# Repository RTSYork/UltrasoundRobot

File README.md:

Ultrasonic Array for Maze Robot
----
Phil Greenland and Russell Joyce  
Department of Computer Science, University of York, UK

---

For more information, see http://rtslab.wikispaces.com/Ultrasonic+Array+for+Maze+Robot

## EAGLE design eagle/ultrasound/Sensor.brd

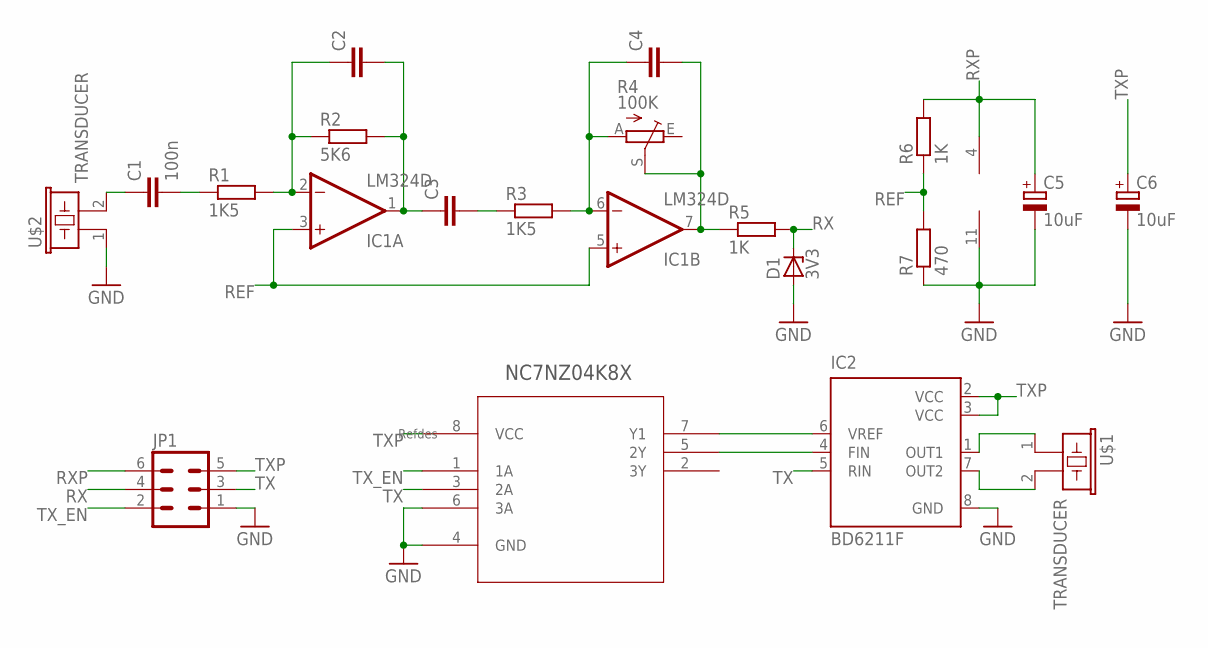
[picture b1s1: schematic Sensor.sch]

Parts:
C1: 100n; C0805
C2, C3, C4: C-EUC0805; C0805
C5, C6: 10uF; E2-5
D1: 3V3; ZDIO-2.5
IC1: LM324D; SO14
IC2: BD6211F; SOP8
JP1: MA03-2
R1, R3: 1K5; R0805
R2: 5K6; R0805
R4: 100K; S63P
R5, R6: 1K; R0805
R7: 470; R0805
U1: NC7NZ04K8X; SOP50P310X90-8N
U$1, U$2: TRANSDUCER

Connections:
GND: C5.-, C6.-, D1.A, IC1.11 (V-), IC2.8 (GND), JP1.1, R7.1, U1.4 (GND), U1.6 (3A), U$2.1
unnamed: C2.1, IC1.2 (-IN), R1.2, R2.1
unnamed: C1.2, R1.1
unnamed: C2.2, C3.1, IC1.1 (OUT), R2.2
unnamed: C3.2, R3.1
unnamed: C4.1, IC1.6 (-IN), R3.2, R4.A
unnamed: C4.2, IC1.7 (OUT), R4.S, R5.1
unnamed: C1.1, U$2.2
unnamed: IC2.1 (OUT1), U$1.1
unnamed: IC2.7 (OUT2), U$1.2
unnamed: IC2.6 (VREF), U1.7 (Y1)
unnamed: IC2.4 (FIN), U1.5 (2Y)
REF: IC1.3 (+IN), IC1.5 (+IN), R6.1, R7.2
RX: D1.C, JP1.4, R5.2
RXP: C5.+, IC1.4 (V+), JP1.6, R6.2
TX: IC2.5 (RIN), JP1.3, U1.3 (2A)
TXP: C6.+, IC2.2 (VCC), IC2.3 (VCC), JP1.5, U1.8 (VCC)
TX_EN: JP1.2, U1.1 (1A)

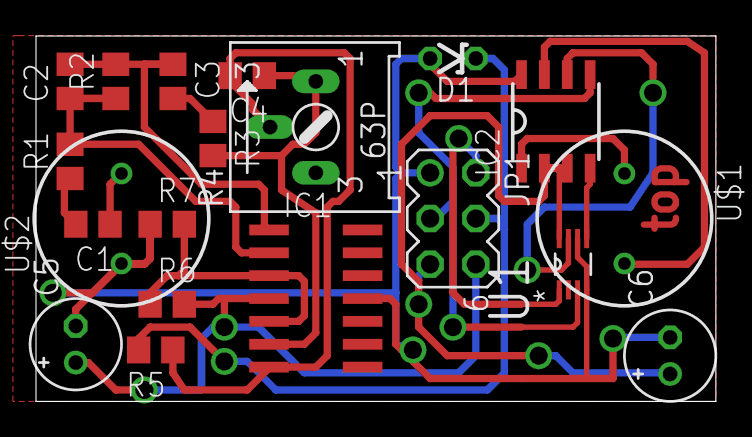
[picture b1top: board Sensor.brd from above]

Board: 2 copper layers, 37.8 x 20.3 mm, 20 parts (0 on the bottom side), 18 nets.

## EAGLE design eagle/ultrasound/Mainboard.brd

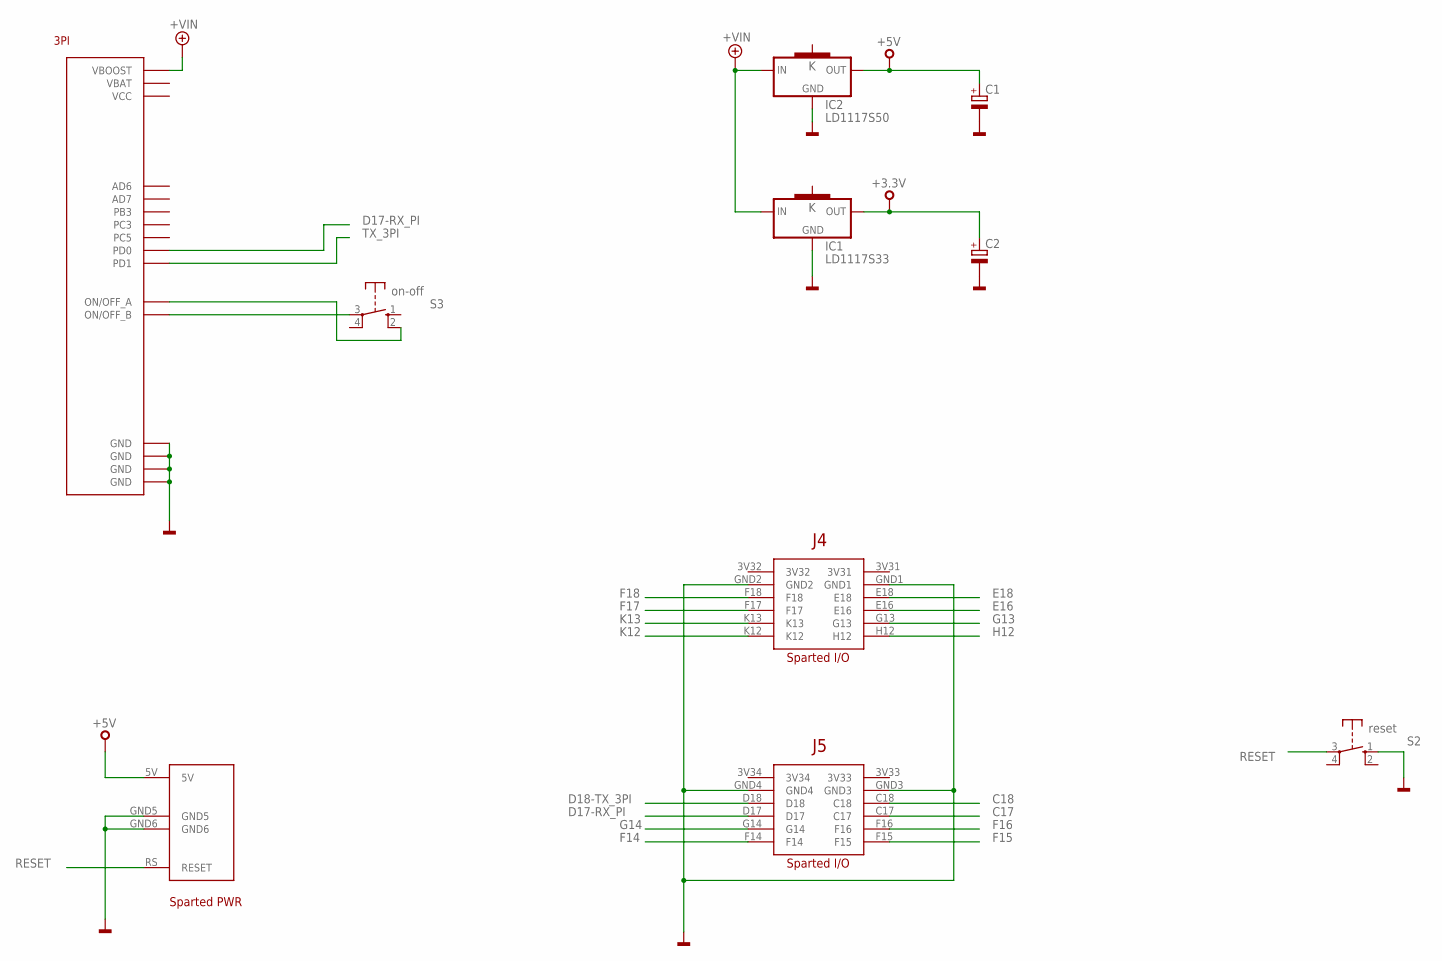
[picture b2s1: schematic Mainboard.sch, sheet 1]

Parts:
C1, C2: CPOL-EUE2.5-5; E2,5-5
IC1: LD1117S33; SOT223
IC2: LD1117S50; SOT223
S2: reset; DT6
S3: on-off; DT6
U$1: M3PI-NO-LCD
U$4: LX9

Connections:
+3,3V: C2.+, IC1.2 (OUT)
+5V: C1.+, IC2.2 (OUT), U$4.5V; also elsewhere on the board
+VIN: IC1.3 (IN), IC2.3 (IN), U$1.VBOOST
C17: U$4.C17; also elsewhere on the board
C18: U$4.C18; also elsewhere on the board
D17-RX_PI: U$1.PD0, U$4.D17
D18-TX_3PI: U$4.D18; also elsewhere on the board
E16: U$4.E16; also elsewhere on the board
E18: U$4.E18; also elsewhere on the board
F14: U$4.F14; also elsewhere on the board
F15: U$4.F15; also elsewhere on the board
F16: U$4.F16; also elsewhere on the board
F17: U$4.F17; also elsewhere on the board
F18: U$4.F18; also elsewhere on the board
G13: U$4.G13; also elsewhere on the board
G14: U$4.G14; also elsewhere on the board
GND: C1.-, C2.-, IC1.1 (GND), IC2.1 (GND), S2.1 (S), U$1.GND@1 (GND), U$1.GND@2 (GND), U$1.GND@3 (GND), U$1.GND@4 (GND), U$4.GND1, U$4.GND2, U$4.GND3, U$4.GND4, U$4.GND5, U$4.GND6; also elsewhere on the board
H12: U$4.H12; also elsewhere on the board
K12: U$4.K12; also elsewhere on the board
K13: U$4.K13; also elsewhere on the board
unnamed: S3.3, U$1.ON/OFF_B
unnamed: S3.2 (S), U$1.ON/OFF_A
RESET: S2.3, U$4.RS (RESET)
TX_3PI: U$1.PD1; also elsewhere on the board

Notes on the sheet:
Sparted I/O
Sparted PWR

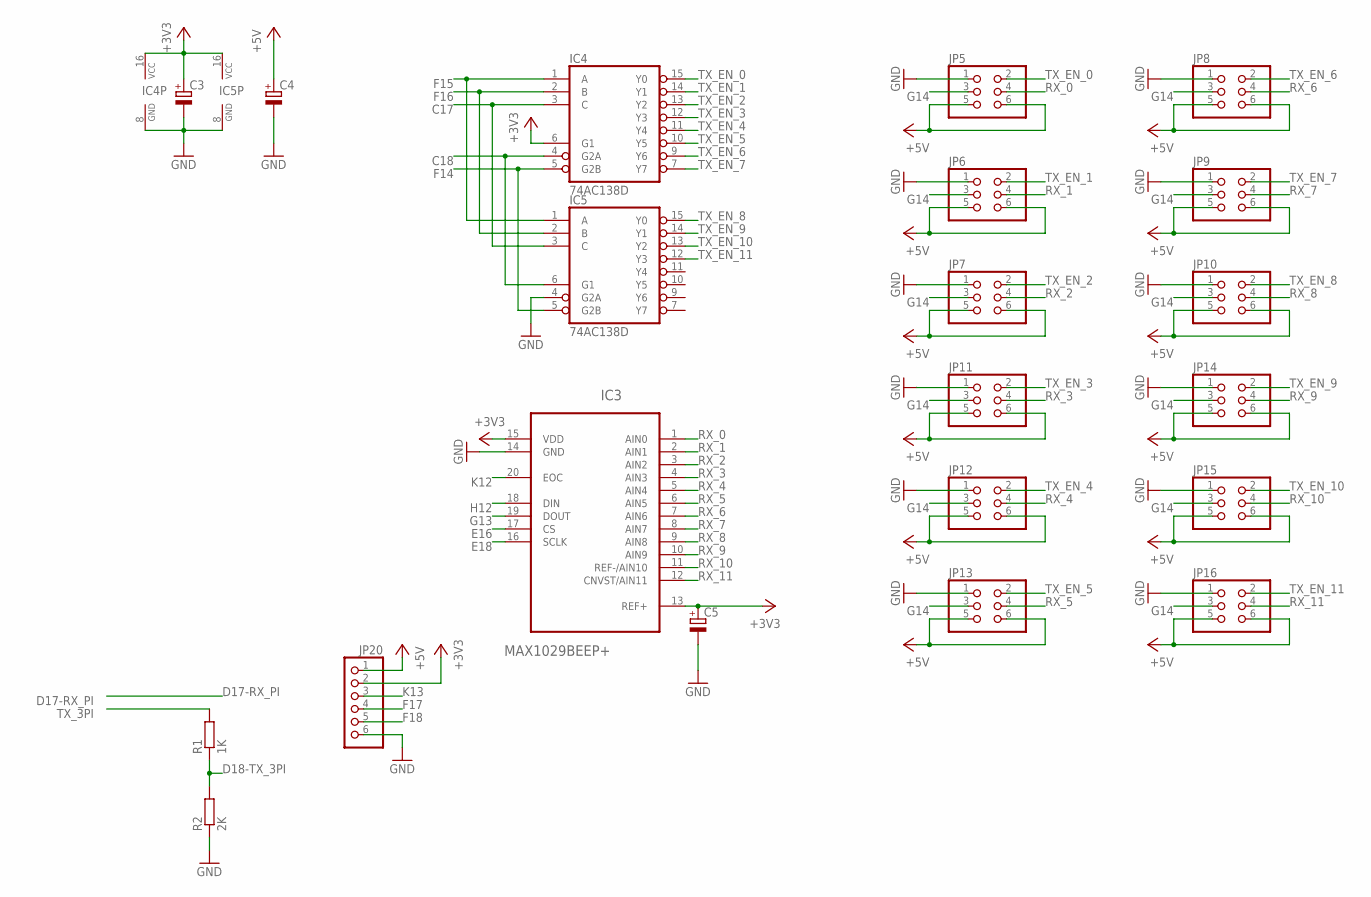
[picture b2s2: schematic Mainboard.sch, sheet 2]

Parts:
C3, C4, C5: CPOL-EUE2-5; E2-5
IC3: MAX1029BEEP+; SOP64P600X165-20N
IC4, IC5: 74AC138D; SO16
JP5, JP9: PINHD-2X3; 2X03
JP6, JP7, JP8, JP10, JP11, JP12, JP13, JP14, JP15, JP16: PINHD-2X3/90; 2X03/90
JP20: PINHD-1X6; 1X06
R1: 1K; R0805
R2: 2K; R0805

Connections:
+3V3: C3.+, C5.+, IC3.13 (REF+), IC3.15 (VDD), IC4.6 (G1), IC4.16 (VCC), IC5.16 (VCC), JP20.2
+5V: C4.+, JP5.5, JP5.6, JP6.5, JP6.6, JP7.5, JP7.6, JP8.5, JP8.6, JP9.5, JP9.6, JP10.5, JP10.6, JP11.5, JP11.6, JP12.5, JP12.6, JP13.5, JP13.6, JP14.5, JP14.6, JP15.5, JP15.6, JP16.5, JP16.6, JP20.1; also elsewhere on the board
C17: IC4.3 (C), IC5.3 (C); also elsewhere on the board
C18: IC4.4 (G2A), IC5.6 (G1); also elsewhere on the board
D18-TX_3PI: R1.1, R2.2; also elsewhere on the board
E16: IC3.17 (CS); also elsewhere on the board
E18: IC3.16 (SCLK); also elsewhere on the board
F14: IC4.5 (G2B), IC5.5 (G2B); also elsewhere on the board
F15: IC4.1 (A), IC5.1 (A); also elsewhere on the board
F16: IC4.2 (B), IC5.2 (B); also elsewhere on the board
F17: JP20.4; also elsewhere on the board
F18: JP20.5; also elsewhere on the board
G13: IC3.19 (DOUT); also elsewhere on the board
G14: JP5.3, JP6.3, JP7.3, JP8.3, JP9.3, JP10.3, JP11.3, JP12.3, JP13.3, JP14.3, JP15.3, JP16.3; also elsewhere on the board
GND: C3.-, C4.-, C5.-, IC3.14 (GND), IC4.8 (GND), IC5.4 (G2A), IC5.8 (GND), JP5.1, JP6.1, JP7.1, JP8.1, JP9.1, JP10.1, JP11.1, JP12.1, JP13.1, JP14.1, JP15.1, JP16.1, JP20.6, R2.1; also elsewhere on the board
H12: IC3.18 (DIN); also elsewhere on the board
K12: IC3.20 (EOC); also elsewhere on the board
K13: JP20.3; also elsewhere on the board
RX_0: IC3.1 (AIN0), JP5.4
RX_1: IC3.2 (AIN1), JP6.4
RX_2: IC3.3 (AIN2), JP7.4
RX_3: IC3.4 (AIN3), JP11.4
RX_4: IC3.5 (AIN4), JP12.4
RX_5: IC3.6 (AIN5), JP13.4
RX_6: IC3.7 (AIN6), JP8.4
RX_7: IC3.8 (AIN7), JP9.4
RX_8: IC3.9 (AIN8), JP10.4
RX_9: IC3.10 (AIN9), JP14.4
RX_10: IC3.11 (REF-/AIN10), JP15.4
RX_11: IC3.12 (CNVST/AIN11), JP16.4
TX_3PI: R1.2; also elsewhere on the board
TX_EN_0: IC4.15 (Y0), JP5.2
TX_EN_1: IC4.14 (Y1), JP6.2
TX_EN_2: IC4.13 (Y2), JP7.2
TX_EN_3: IC4.12 (Y3), JP11.2
TX_EN_4: IC4.11 (Y4), JP12.2
TX_EN_5: IC4.10 (Y5), JP13.2
TX_EN_6: IC4.9 (Y6), JP8.2
TX_EN_7: IC4.7 (Y7), JP9.2
TX_EN_8: IC5.15 (Y0), JP10.2
TX_EN_9: IC5.14 (Y1), JP14.2
TX_EN_10: IC5.13 (Y2), JP15.2
TX_EN_11: IC5.12 (Y3), JP16.2

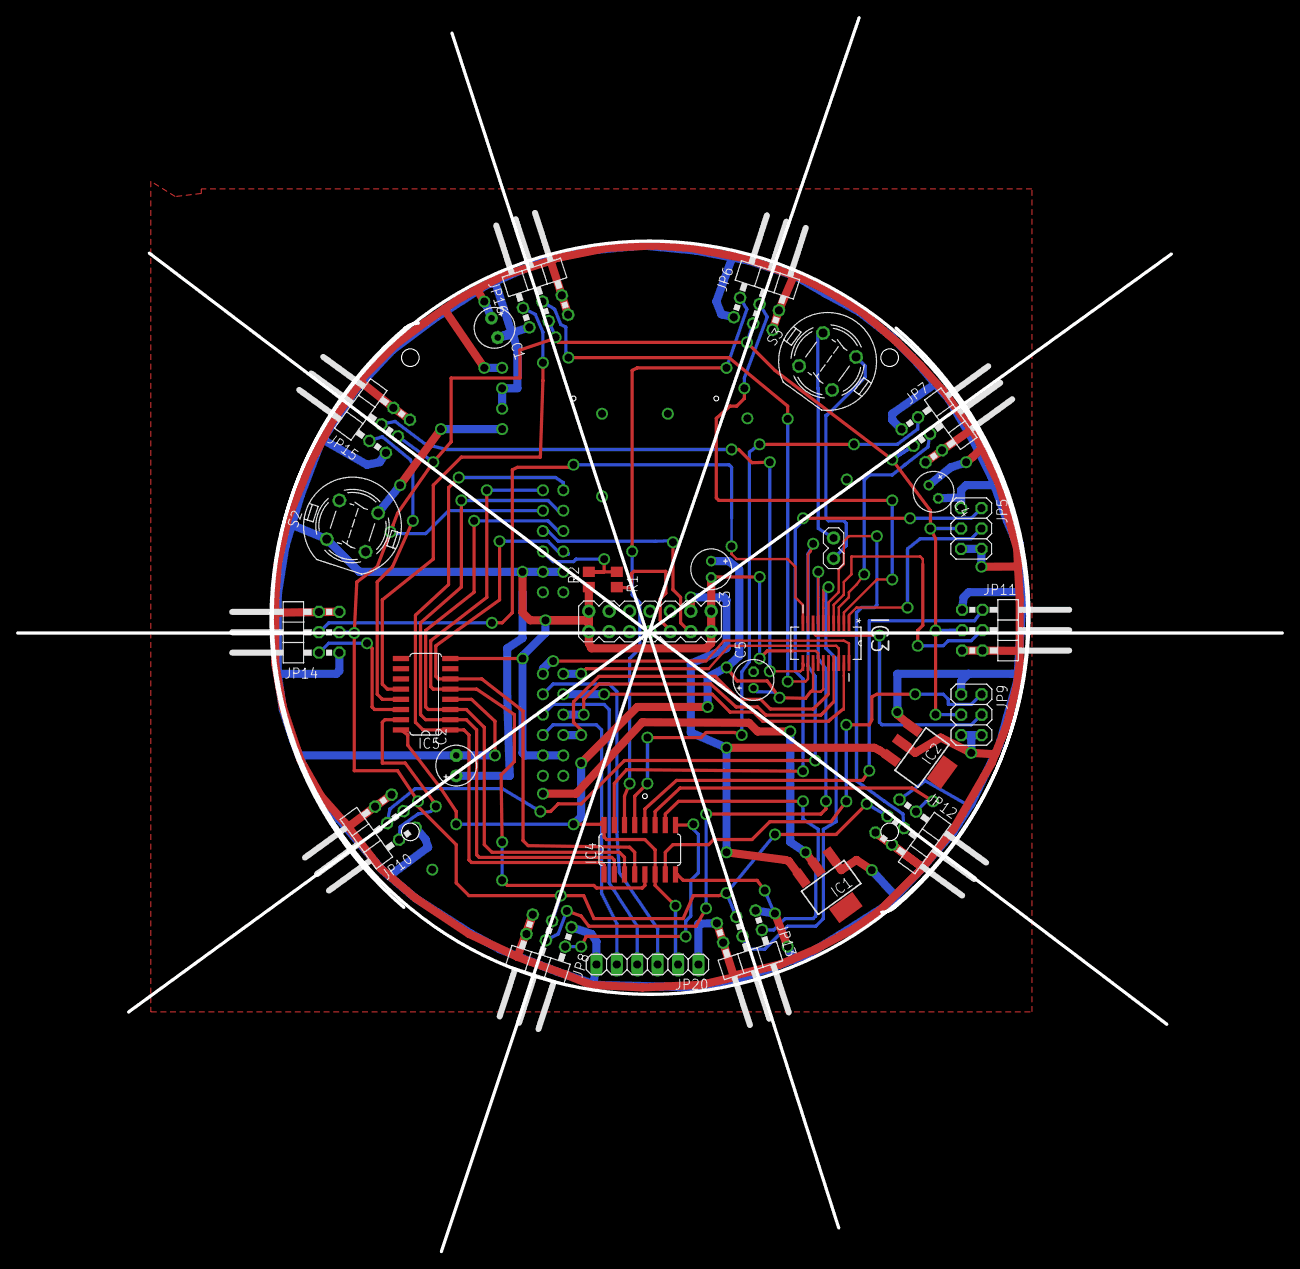
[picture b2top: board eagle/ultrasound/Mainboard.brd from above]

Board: 2 copper layers, 157.5 x 153.7 mm, 29 parts (1 on the bottom side), 49 nets.

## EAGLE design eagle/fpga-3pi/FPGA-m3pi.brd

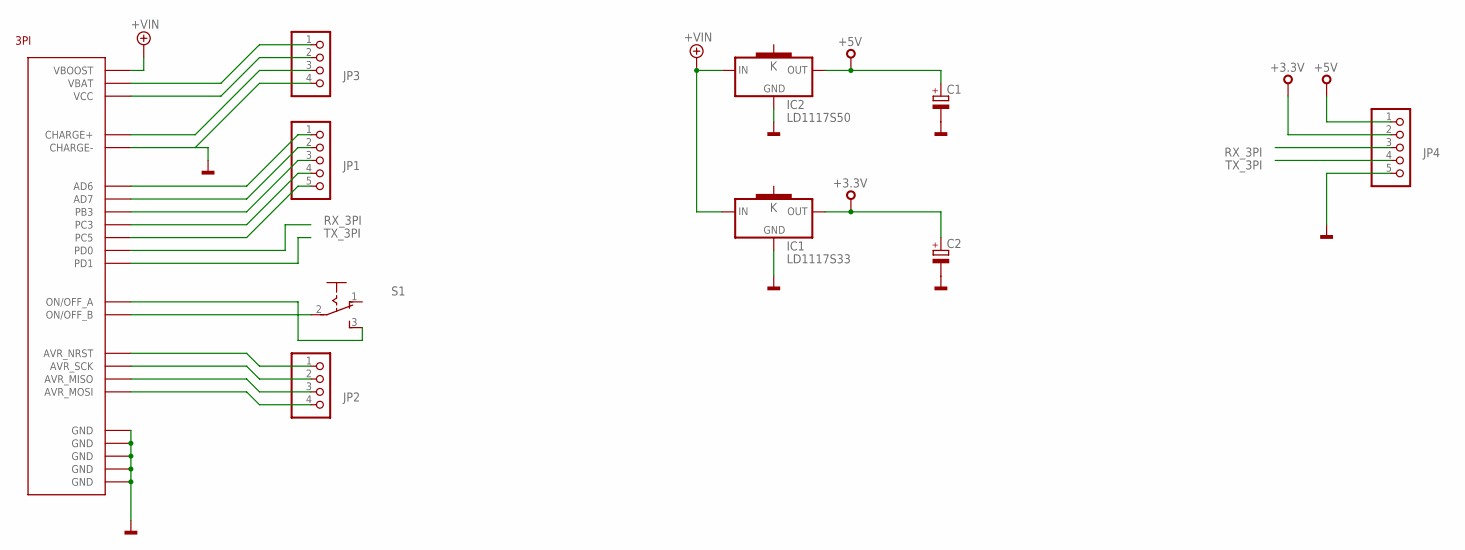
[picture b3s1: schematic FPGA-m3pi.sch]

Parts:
C1, C2: CPOL-EUE2.5-5; E2,5-5
IC1: LD1117S33; SOT223
IC2: LD1117S50; SOT223
JP1, JP4: PINHD-1X5; 1X05
JP2, JP3: PINHD-1X4; 1X04
S1: M251
U$1: MBED-M3PI_3PI

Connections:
+3,3V: C2.+, IC1.2 (OUT), JP4.2
+5V: C1.+, IC2.2 (OUT), JP4.1
+VIN: IC1.3 (IN), IC2.3 (IN), U$1.VBOOST
GND: C1.-, C2.-, IC1.1 (GND), IC2.1 (GND), JP3.4, JP4.5, U$1.CHARGE-, U$1.GND@1 (GND), U$1.GND@2 (GND), U$1.GND@3 (GND), U$1.GND@4 (GND), U$1.GND@5 (GND)
unnamed: JP1.1, U$1.AD6
unnamed: JP1.2, U$1.AD7
unnamed: S1.2, U$1.ON/OFF_B
unnamed: S1.3 (S), U$1.ON/OFF_A
unnamed: JP1.3, U$1.PB3
unnamed: JP1.4, U$1.PC3
unnamed: JP1.5, U$1.PC5
unnamed: JP2.1, U$1.AVR_NRST
unnamed: JP2.2, U$1.AVR_SCK
unnamed: JP2.3, U$1.AVR_MISO
unnamed: JP2.4, U$1.AVR_MOSI
unnamed: JP3.3, U$1.CHARGE+
unnamed: JP3.2, U$1.VCC
unnamed: JP3.1, U$1.VBAT
RX_3PI: JP4.3, U$1.PD0
TX_3PI: JP4.4, U$1.PD1

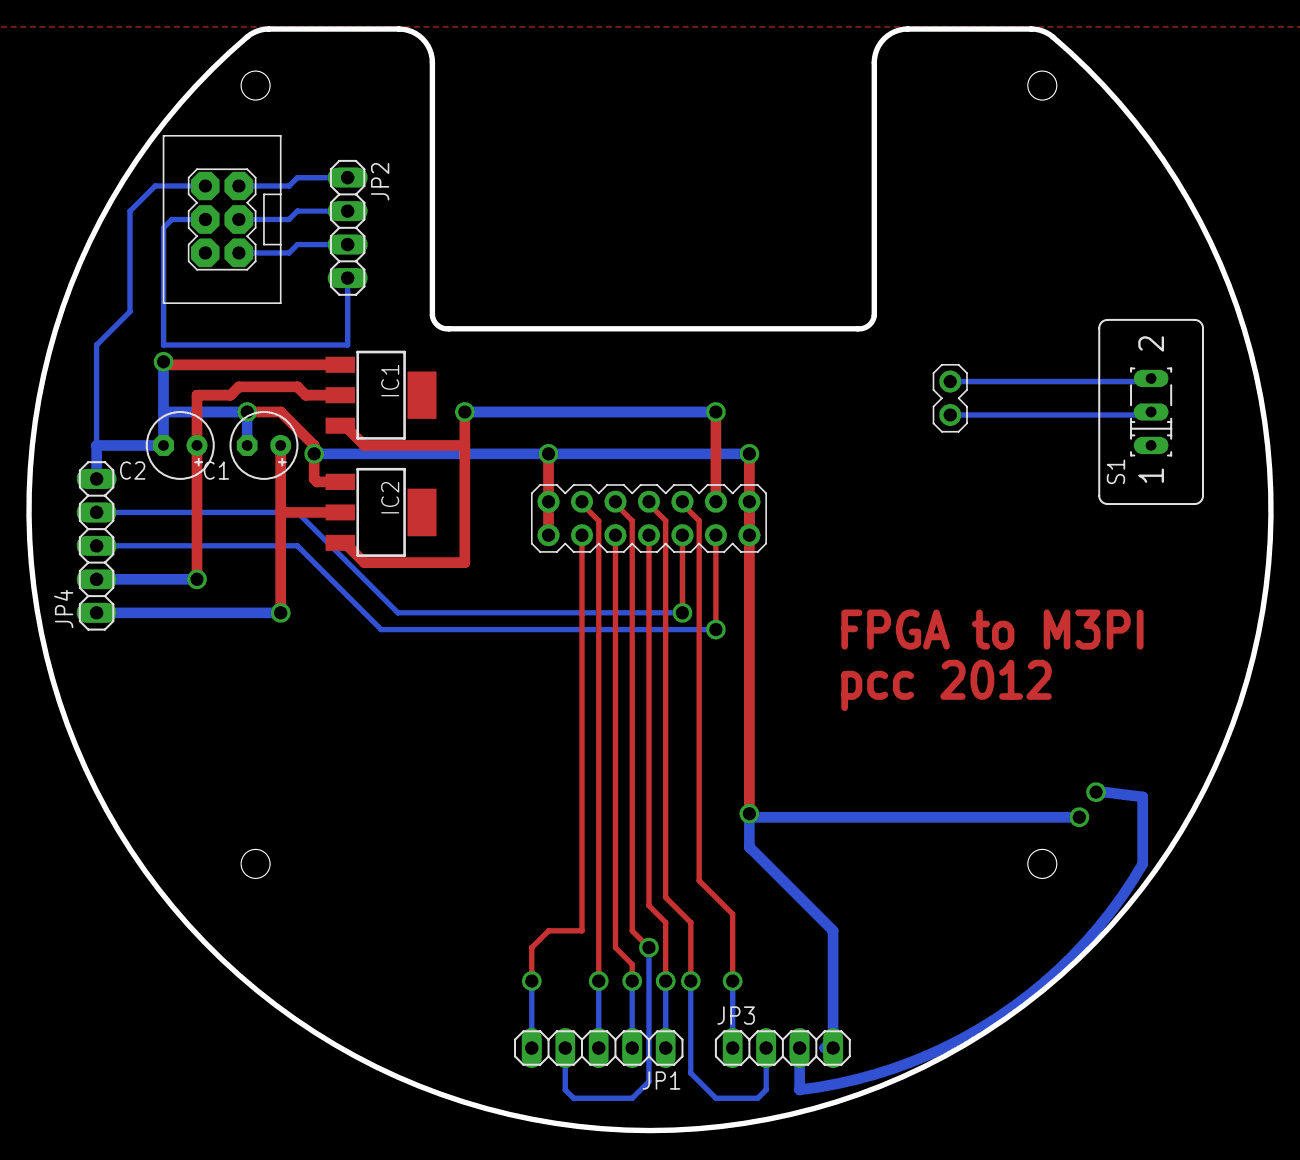
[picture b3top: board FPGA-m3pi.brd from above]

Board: 2 copper layers, 94.2 x 83.6 mm, 10 parts (0 on the bottom side), 20 nets.

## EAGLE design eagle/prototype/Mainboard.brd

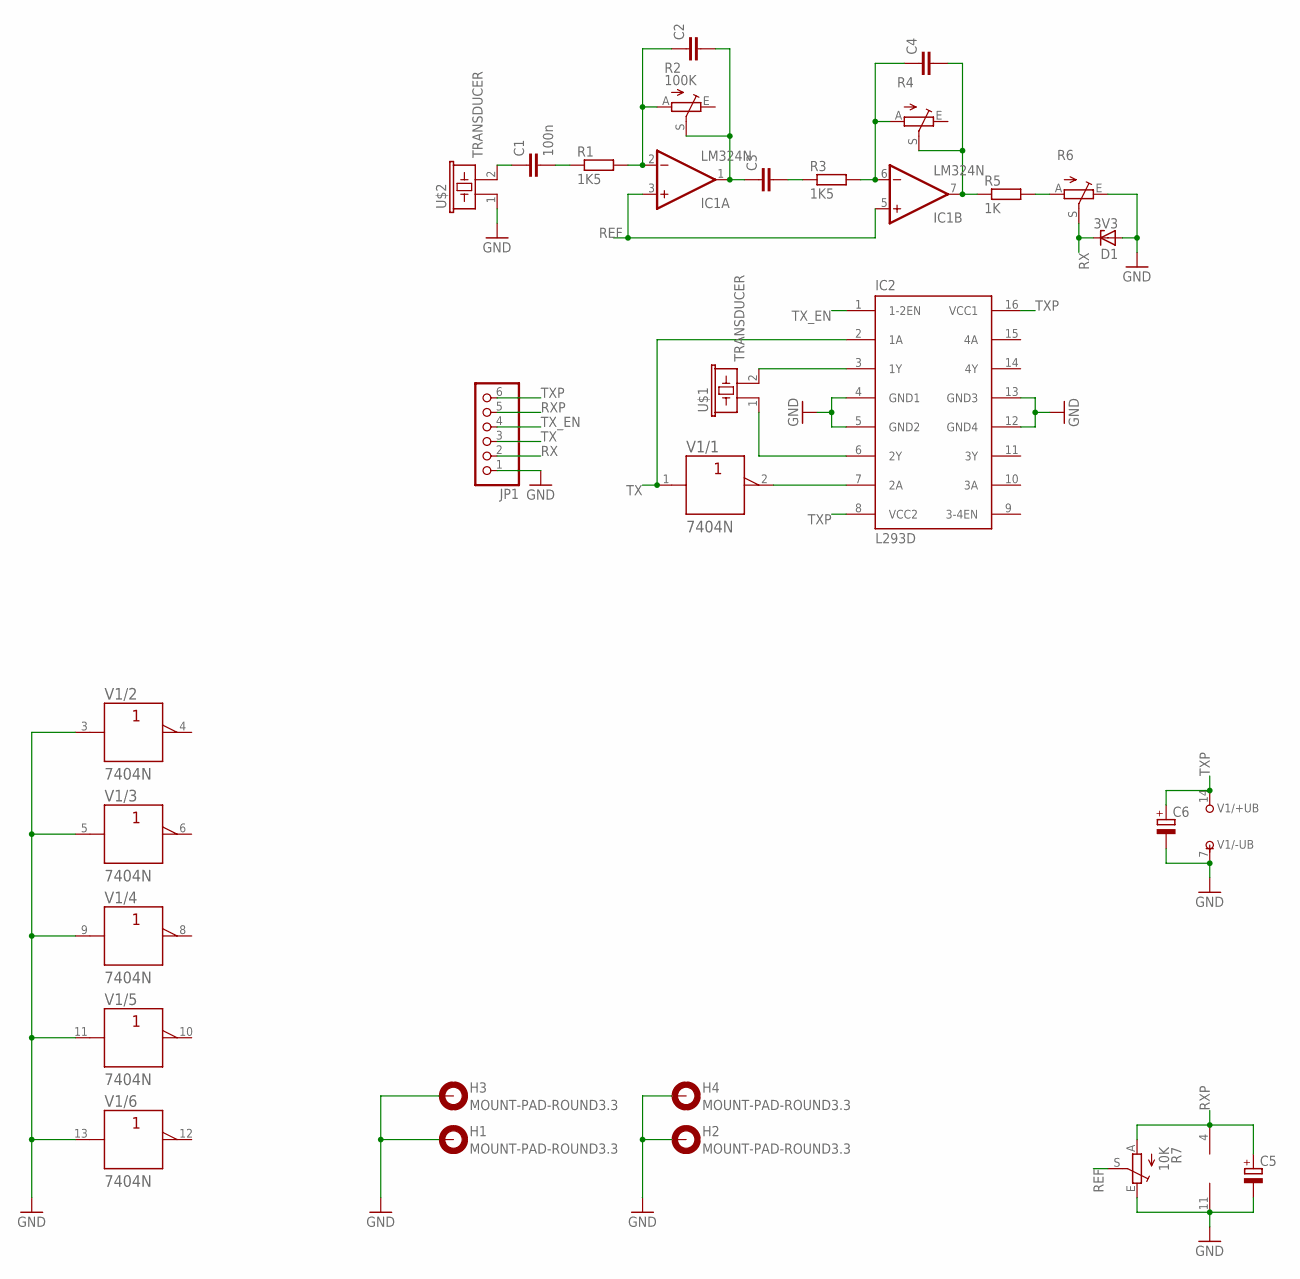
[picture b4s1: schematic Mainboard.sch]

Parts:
C1: 100n; C025-025X050
C2, C3, C4: C-EU025-025X050; C025-025X050
C5, C6: CPOL-EUE2-5; E2-5
D1: 3V3; ZDIO-2.5
H1, H2, H3, H4: MOUNT-PAD-ROUND3.3; 3,3-PAD
IC1: LM324N; DIL14
IC2: L293D; DIL16
JP1: PINHD-1X6; 1X06
R1, R3: 1K5; 0207/2V
R2: 100K; S63P
R4, R6: TRIM_EU-S63P; S63P
R5: 1K; 0207/2V
R7: 10K; S63P
U$1, U$2: TRANSDUCER
V1: 7404N; DIL14

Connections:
GND: C5.-, C6.-, D1.A, H1.B3,3, H2.B3,3, H3.B3,3, H4.B3,3, IC1.11 (V-), IC2.4 (GND1), IC2.5 (GND2), IC2.12 (GND4), IC2.13 (GND3), JP1.1, R6.E, R7.E, U$2.1, V1.3 (A), V1.5 (A), V1.7 (-UB), V1.9 (A), V1.11 (A), V1.13 (A)
unnamed: C2.1, IC1.2 (-IN), R1.2, R2.A
unnamed: C1.2, R1.1
unnamed: C2.2, C3.1, IC1.1 (OUT), R2.S
unnamed: R5.2, R6.A
unnamed: C3.2, R3.1
unnamed: C4.1, IC1.6 (-IN), R3.2, R4.A
unnamed: C4.2, IC1.7 (OUT), R4.S, R5.1
unnamed: IC2.7 (2A), V1.2 (Y)
unnamed: C1.1, U$2.2
unnamed: IC2.3 (1Y), U$1.2
unnamed: IC2.6 (2Y), U$1.1
REF: IC1.3 (+IN), IC1.5 (+IN), R7.S
RX: D1.C, JP1.2, R6.S
RXP: C5.+, IC1.4 (V+), JP1.5, R7.A
TX: IC2.2 (1A), JP1.3, V1.1 (A)
TXP: C6.+, IC2.8 (VCC2), IC2.16 (VCC1), JP1.6, V1.14 (+UB)
TX_EN: IC2.1 (1-2EN), JP1.4

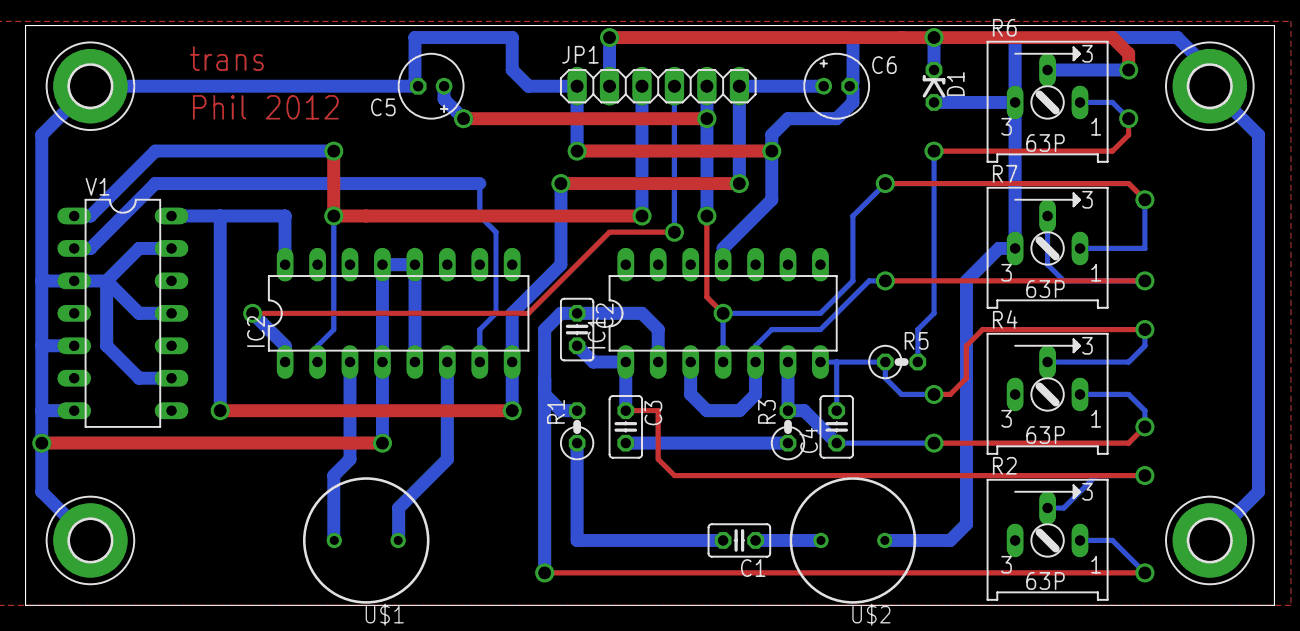
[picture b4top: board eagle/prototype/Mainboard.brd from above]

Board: 2 copper layers, 97.8 x 45.4 mm, 24 parts (0 on the bottom side), 18 nets.

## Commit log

2013-04-19 Added report
2013-04-19 Added 3D printed wheels and encoder template
2013-04-19 Added CAD diagrams
2013-04-19 Added maze diagrams
2013-04-19 Added ultrasound code for arduino and mbed, with processing code
2013-04-19 Added 3PI code
2013-04-26 Added eagle diagrams
2013-04-27 Renamed report eagle schematics to match figures.
2013-04-28 Continued design and implementation adding receiver amp and filters.
2013-04-29 Continued design and implementation.
2013-04-29 Removed pot from blueboard schematic.
2013-04-29 Updated processing app, changed trigger base, changed default triggers and added flag to disable center line.
2013-04-29 Refactored processing app, fixed bug with echo first time.
2013-04-29 Converted RT to direct distance, turned off useless labels.
2013-04-29 Changed speed of sound in processing app.
2013-04-29 Added window title and changed default window size for screenshots.
2013-05-01 Continued design and implementation, completing all range finder diagrams.
2013-05-02 Updated component values on daughter board schematic to match actual board.
2013-05-02 Added positioning system to design and implementation.
2013-05-04 Added 3D robot diagram :-).
2013-05-04 Increased daughter board count to 28 and decreased width.
2013-05-04 Added 3D robot diagram to report.
2013-05-05 Compacted diagrams and headings. Changed word count format. Updated report page plan. Remoed mobile platform from design. Added placeholder software flow diagrams.
2013-05-08 Added split triggers to ultrasound_processing.
2013-05-08 Improved timing.
2013-05-08 Added cycle counter and running minimum time for first peaks.
2013-05-09 Removed useless max and min peak indicators. Refactored a bit.
2013-05-09 Tweaked timing on mbed.
2013-05-09 Added temperature compensation to processing app, fixed trigger levels.
2013-05-13 Finished mobile platform software.
2013-05-16 Added FPGA settings.
2013-05-16 Fixed bug, swapping line colours
2013-05-16 Moved original processing script, created new script for distance measurements.
2013-05-17 Tweaked waveform triggering to match FPGA.
2013-05-17 Completed distance app.
2013-05-18 Tweaked various bits of design and implementation. Reduced font size on all diagrams and adjusted diagrams accordingly.
2013-05-19 Added ultrsound_fpga project at last.
2013-05-19 Completed 3PI software.
2013-05-19 Added additional features to Microblaze software.
2013-05-20 Bug fixes and tweaks to 3pi software.
2013-05-20 Bug fixes and additional features for ultrasound_fpga.
2013-05-20 Modified processing apps to accept new data format.
2013-05-20 Modified mbed and arduino apps to supply new data format.
2013-08-06 Normalised line endings and permissions
2013-08-06 Added general .gitignore
2013-08-06 Added .gitignore for XPS/ISE project
2013-08-06 Updated XPS and ISE projects to 14.6
2013-08-06 Added .gitignore for Xilinx SDK
2013-08-06 Added README for GitHub
2013-08-06 Updated Distance and Waveform programs Now use new data format from MicroBlaze, fixes bugs
2013-08-06 Updated sensor board resistor value in Eagle files
2013-08-06 Changed USB UART speed to 57600bps
2013-08-06 Updated 'pulsegen' FPGA core Added parameter for pulse frequency
2013-08-06 Made 'map' and 'par' synthesis steps use 2 threads
2013-08-06 Added Ultrasound Receiver FPGA core (Also includes other MHS changes)
2013-08-06 Updated MicroBlaze code to use 'us_receiver' core Includes changes to other areas of MicroBlaze code
2013-08-07 Tidied up library includes in Xilinx SDK
2013-08-07 Changed serial baud rate of Pololu to 57600
2013-08-07 Increased BRAM size & moved MicroBlaze code there Changed variables from being 'volatile' so code fits in BRAMs
2013-08-07 Moved mobile platform MB code to seperate file
2013-08-07 Added test code for robot movement based on US
2013-08-08 Removed extra range offset for sensors 0 and 5 Hardware has been changed so they are now the same as all other sensors
2013-08-08 Tidied up code for ultrasound detection, etc. Also tidied up some old bits of code
2013-08-08 Changed how sensors are selected for sampling Now allows for an array of sensors to be specified
2013-08-08 Added obstacle detection function Returns if an item is detected within Xmm of a sensor
2013-08-08 Added constants for robot motor direction
2013-08-08 Reduced the number of US samples from 400 to 200 Quicker to sample and still sufficient for small distances
2013-08-08 Changed robot motion to navigate basic maze Turns in the direction that is clear when meets obstacle
2013-08-09 Moved MicroBlaze code into DDR Not enough space in BRAMs any more
2013-08-09 Reduced constant offset in US range calulation
2013-08-09 Added function to get range from US sensor
2013-08-09 Added constants for US sensor positions
2013-08-09 Added state machine for robot driving control Robot avoids walls, turns in the correct direction at a junction
2013-08-12 Removed debug outputs from us_receiver FPGA core
2013-08-12 Added UART for Bluetooth, removed SPI+GPIO cores SPI Flash and Dip Switch cores not needed, changed MB settings for space
2013-08-12 Added Bluetooth UART debug messages Prints the state of the robot movement over Bluetooth UART
